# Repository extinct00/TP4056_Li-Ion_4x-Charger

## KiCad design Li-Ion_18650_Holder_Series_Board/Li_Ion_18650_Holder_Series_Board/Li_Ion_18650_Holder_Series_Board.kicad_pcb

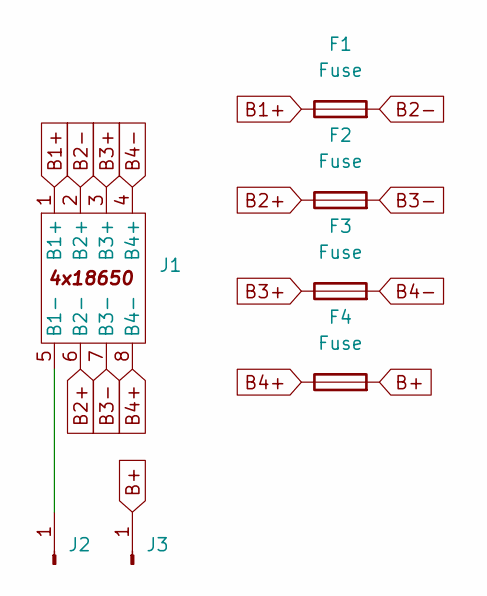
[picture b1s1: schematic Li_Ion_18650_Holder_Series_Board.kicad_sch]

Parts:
F1, F2, F3, F4: Fuse; Fuse_0603_1608Metric; LCSC C41380234
J1: 4xCellHolder_18650
J2, J3: Conn_01x01_Pin; Faston_C27636945; LCSC C27636945

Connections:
B1+: F1.1, J1.1 (B1+)
B2+: F2.1, J1.6 (B2-)
B2-: F1.2, J1.2 (B2+)
B3+: F3.1, J1.3 (B3+)
B3-: F2.2, J1.7 (B3-)
B4+: F4.1, J1.8 (B4-)
B4-: F3.2, J1.4 (B4+)
B+: F4.2, J3.1
unnamed: J1.5 (B1-), J2.1

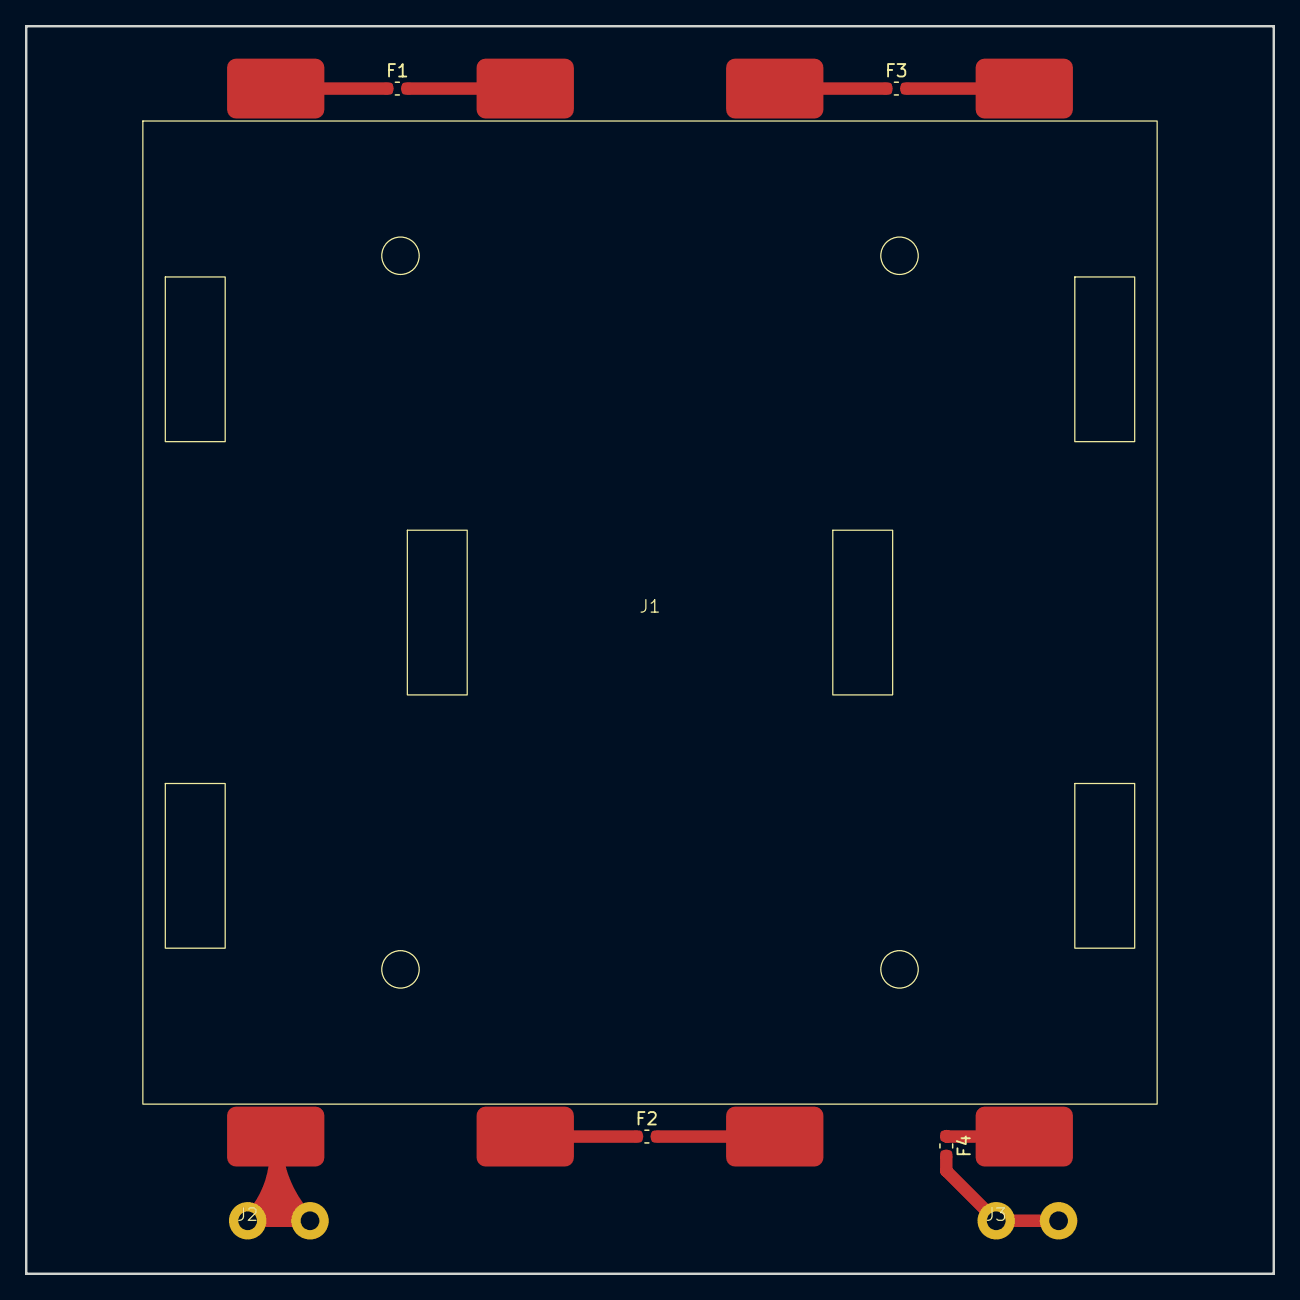
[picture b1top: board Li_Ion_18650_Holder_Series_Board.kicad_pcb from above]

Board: 2 copper layers, 100.0 x 100.0 mm, 7 parts (0 on the bottom side), 9 nets.

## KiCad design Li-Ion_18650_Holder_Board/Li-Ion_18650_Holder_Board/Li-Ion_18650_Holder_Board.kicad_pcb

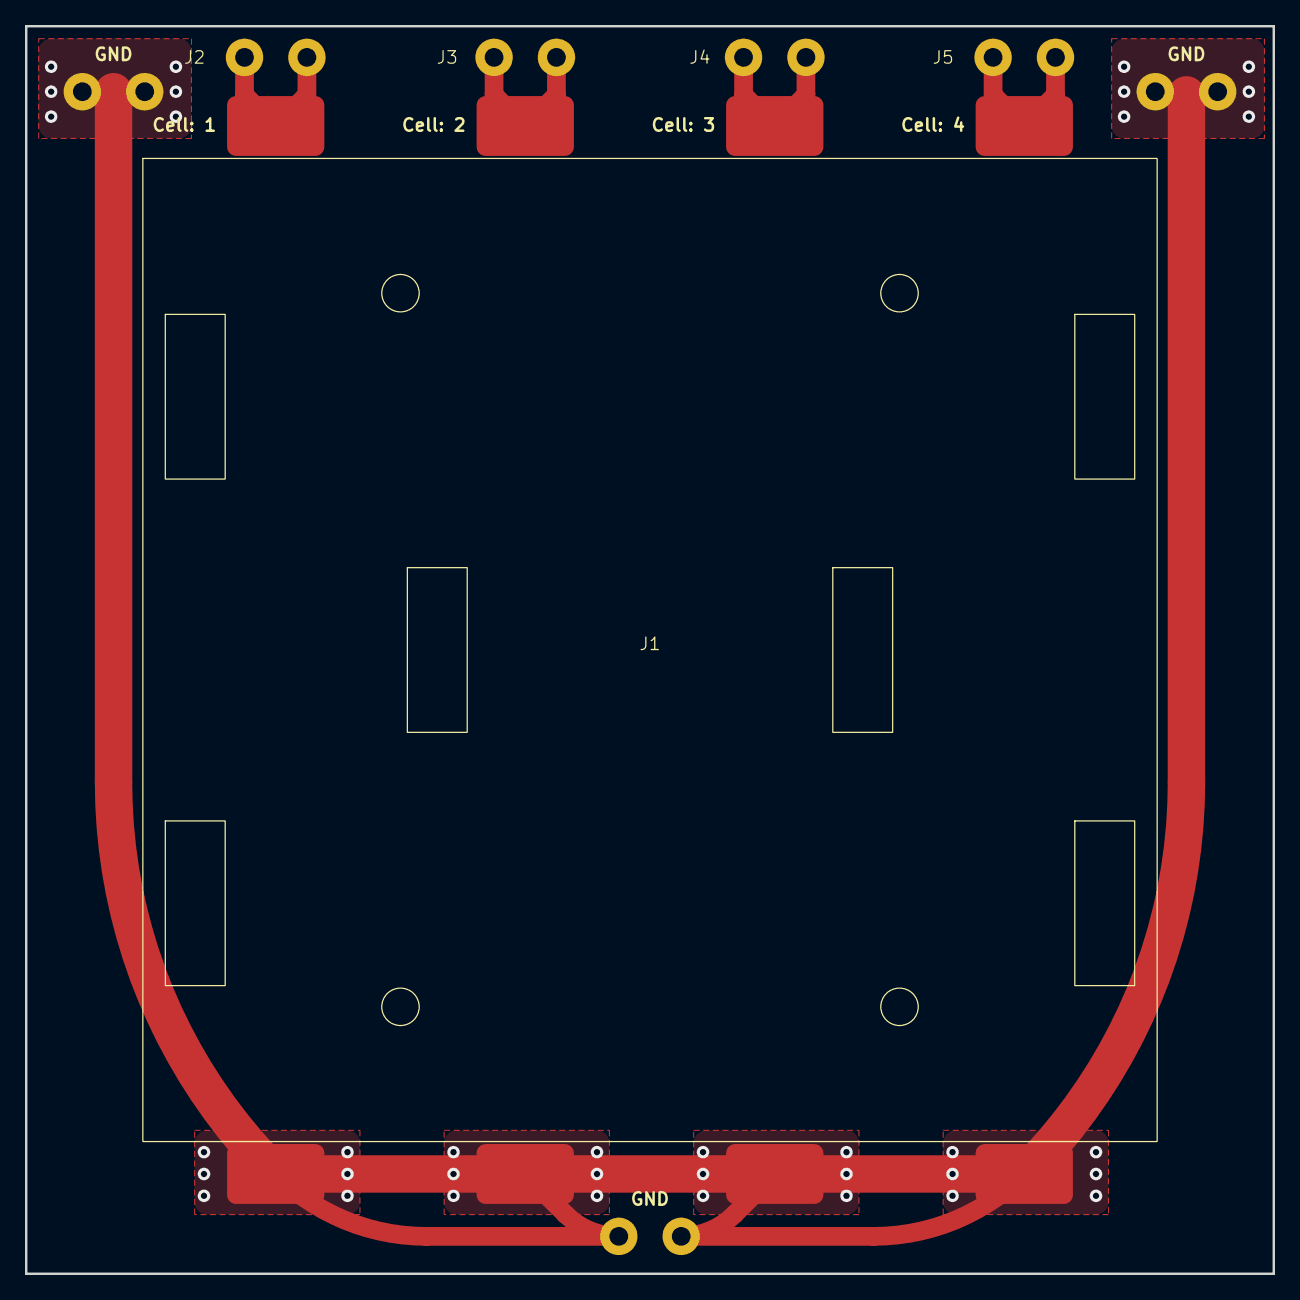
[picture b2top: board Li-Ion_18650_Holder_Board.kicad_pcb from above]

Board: 2 copper layers, 100.0 x 100.0 mm, 8 parts (0 on the bottom side), 5 nets.

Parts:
GND: Conn_01x01_Pin; Faston_C27636945
GND#2, GND#3: Conn_01x01_Pin; Faston_C27636945
J1: 4xCellHolder_18650
J2, J3, J4, J5: Conn_01x01_Pin; Faston_C27636945

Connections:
GND: GND.1, GND#2.1, GND#3.1, J1.5 (B1-), J1.6 (B2-), J1.7 (B3-), J1.8 (B4-)
unnamed: J1.1 (B1+), J2.1
unnamed: J1.2 (B2+), J3.1
unnamed: J1.3 (B3+), J4.1
unnamed: J1.4 (B4+), J5.1

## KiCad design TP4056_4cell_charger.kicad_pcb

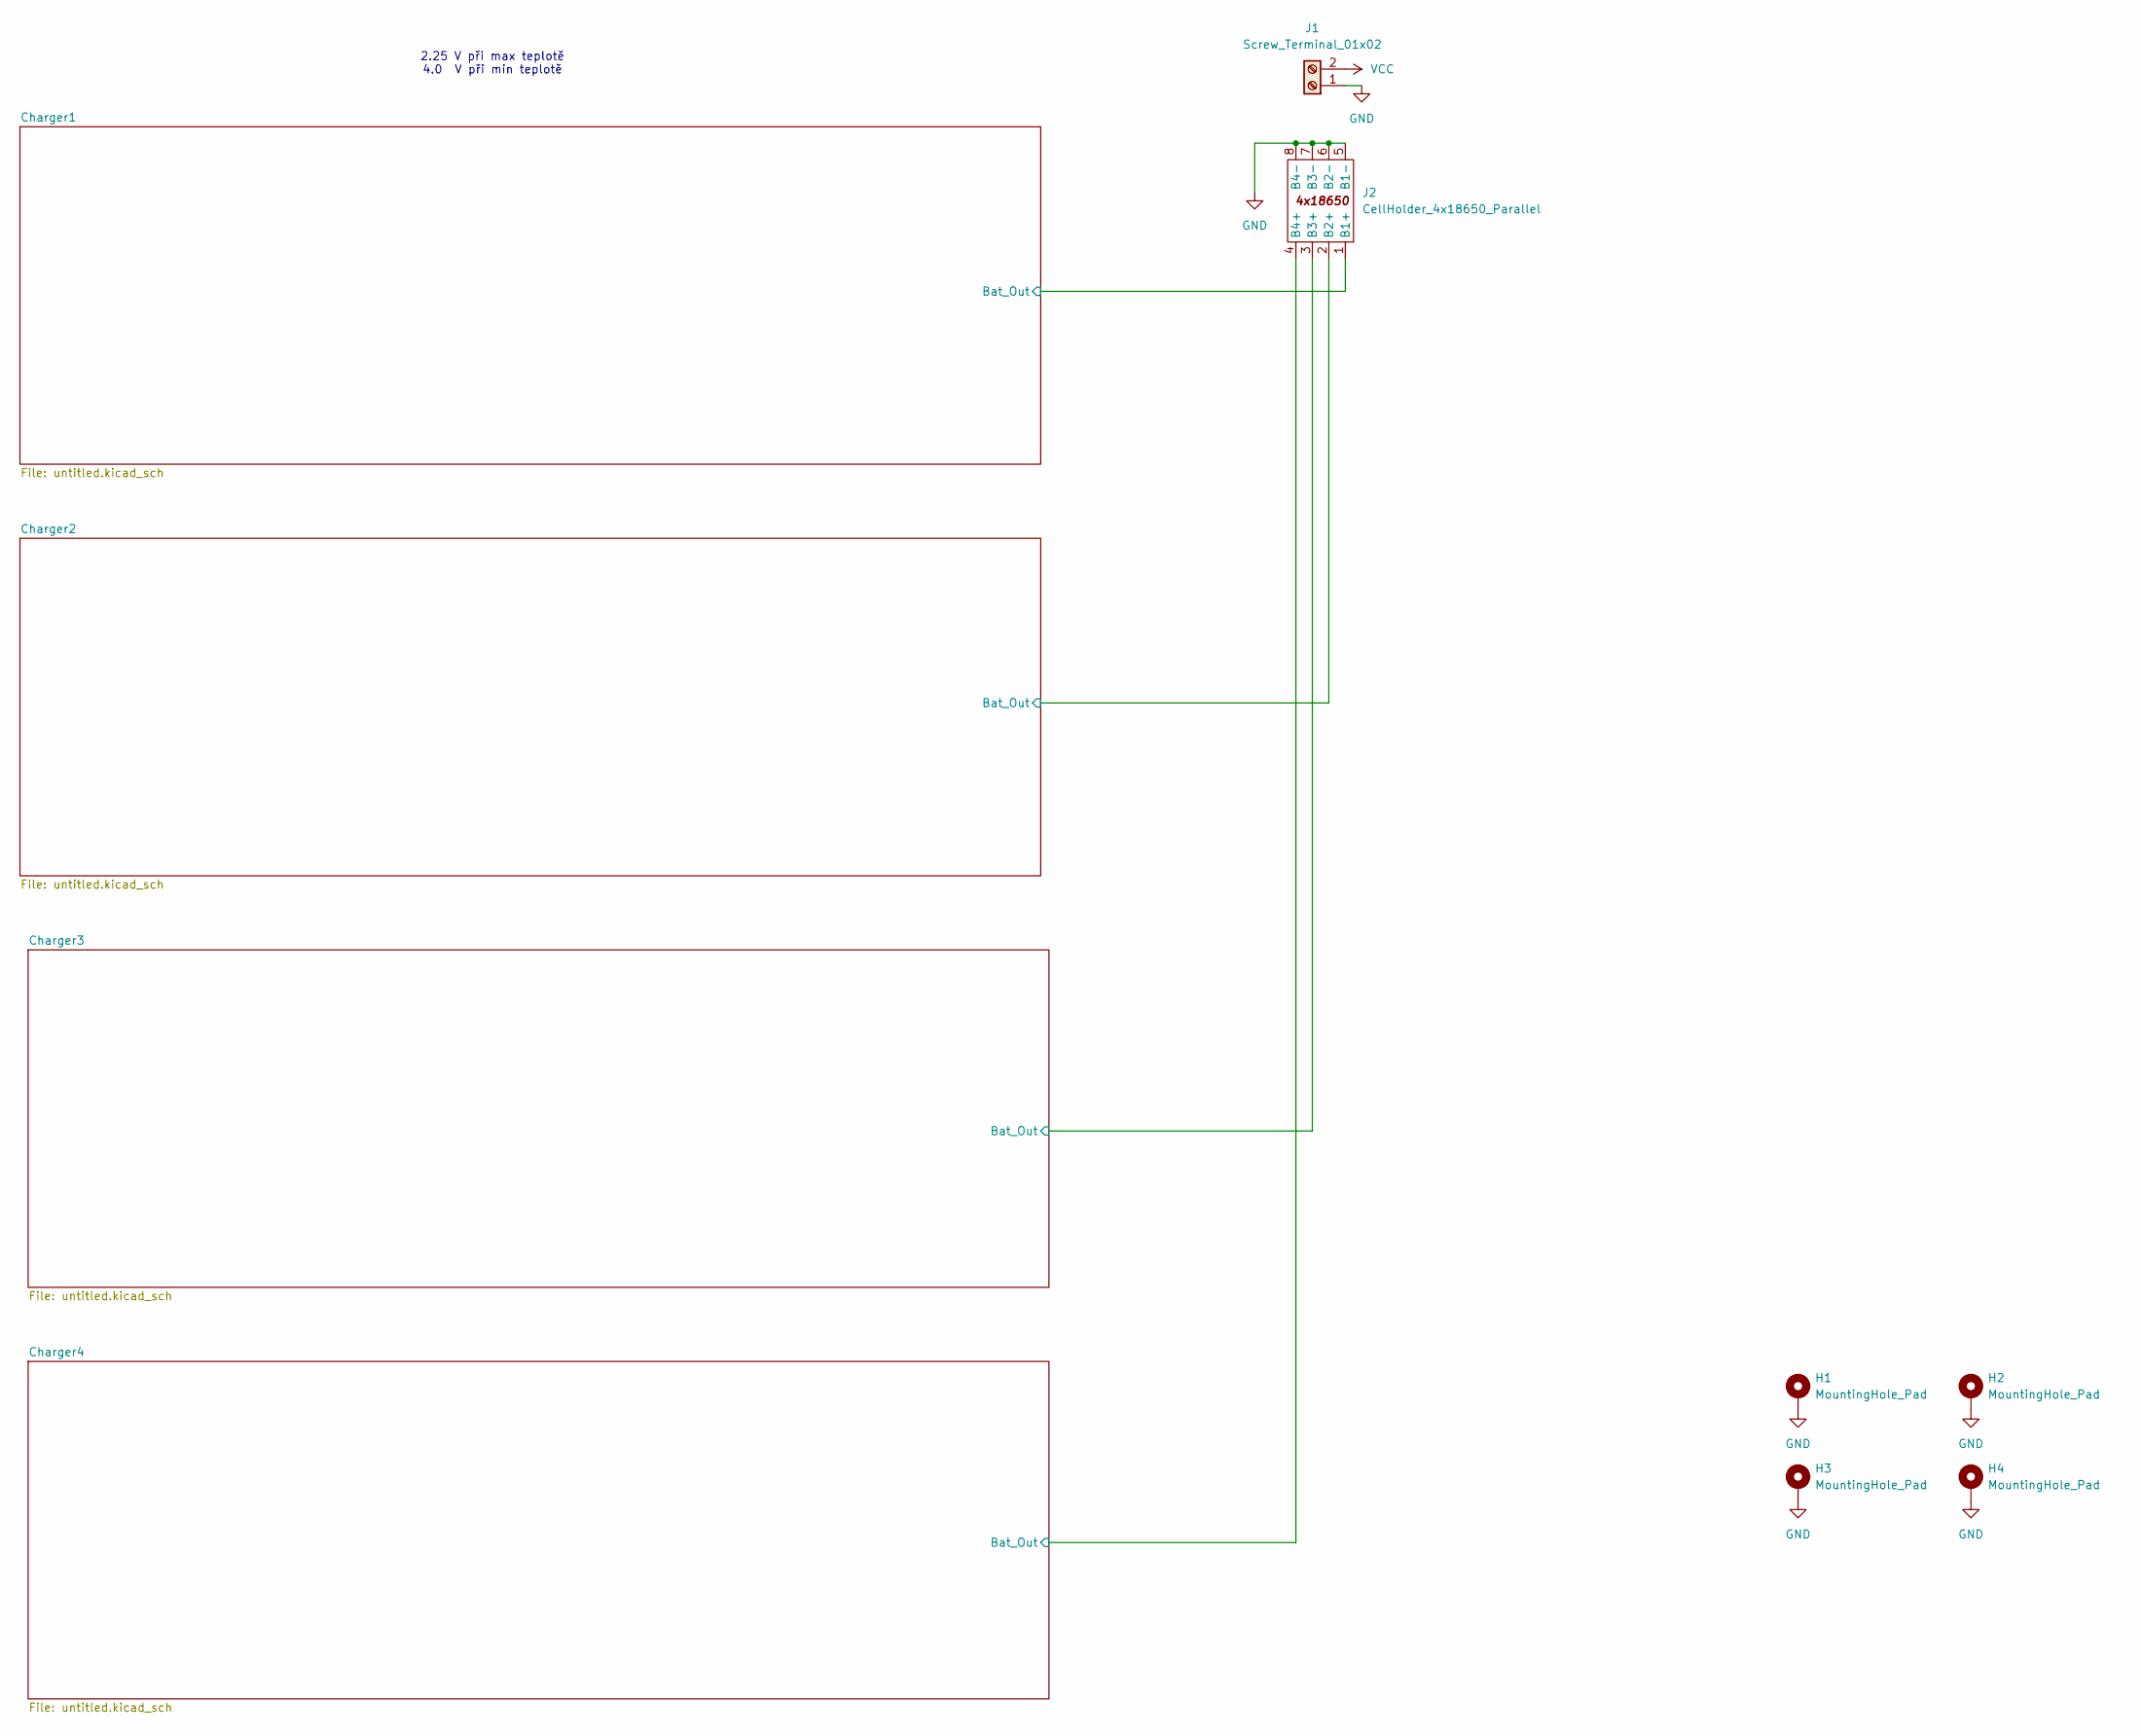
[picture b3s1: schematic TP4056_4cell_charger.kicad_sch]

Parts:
H1, H2, H3, H4: MountingHole_Pad; MountingHole_3.2mm_M3_Pad_Via
J1: Screw_Terminal_01x02; TerminalBlock_Phoenix_MKDS-1,5-2-5.08_1x02_P5.08mm_Horizont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; LCSC C8465
J2: CellHolder_4x18650_Parallel; 4xCellHolder_18650

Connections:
/Charger1/Bat_Out: J2.1 (B1+); also elsewhere on the board
/Charger2/Bat_Out: J2.2 (B2+); also elsewhere on the board
/Charger3/Bat_Out: J2.3 (B3+); also elsewhere on the board
/Charger4/Bat_Out: J2.4 (B4+); also elsewhere on the board
GND: H1.1, H2.1, H3.1, H4.1, J1.1, J2.5 (B1-), J2.6 (B2-), J2.7 (B3-), J2.8 (B4-); also elsewhere on the board
VCC: J1.2; also elsewhere on the board

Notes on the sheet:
2.25 V při max teplotě 4.0 V při min teplotě

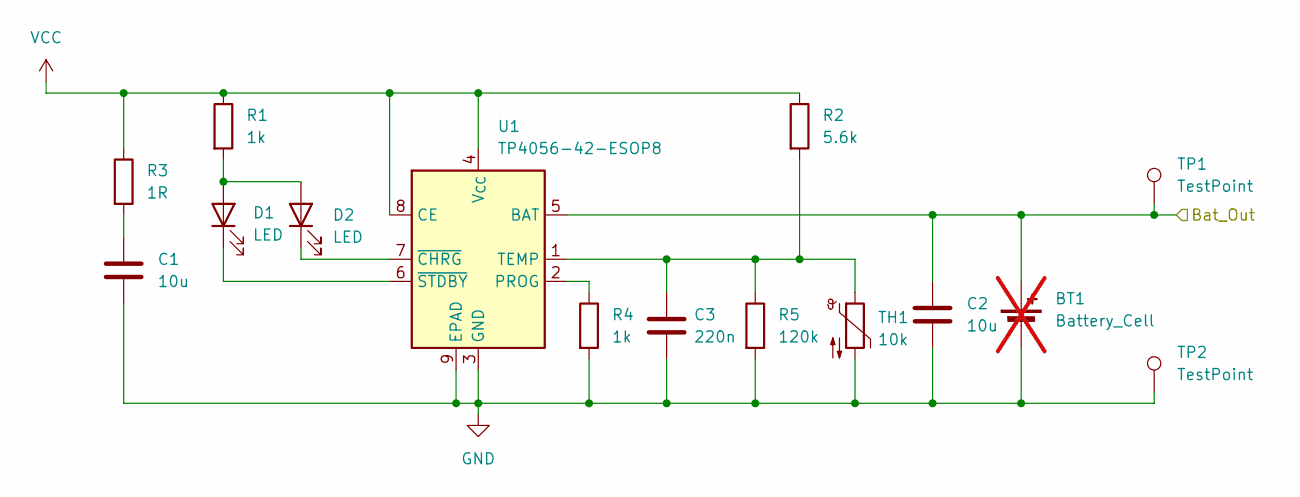
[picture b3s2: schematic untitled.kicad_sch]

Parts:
BT1: Battery_Cell; not fitted
C1, C2: 10u; C_0603_1608Metric; LCSC C19702
C3: 220n; C_0603_1608Metric; LCSC C64705
D1: LED; LED_0603_1608Metric; LCSC C965807
D2: LED; LED_0603_1608Metric; LCSC C965799
R1, R4: 1k; R_0603_1608Metric; LCSC C22548
R2: 5.6k; R_0603_1608Metric; LCSC C114627
R3: 1R; R_0603_1608Metric; LCSC C112305
R5: 120k; R_0603_1608Metric; LCSC C114607
TH1: 10k; R_0603_1608Metric; LCSC C13564
TP1, TP2: TestPoint; TestPoint_Pad_4.0x4.0mm
U1: TP4056-42-ESOP8; SOIC-8-1EP_3.9x4.9mm_P1.27mm_EP2.41x3.3mm_ThermalVias; LCSC C382139

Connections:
/Charger1/Bat_Out: C2.1, TP1.1, U1.5 (BAT); also elsewhere on the board
GND: BT1.2 (-), C1.2, C2.2, C3.2, R4.2, R5.2, TH1.2, TP2.1, U1.3 (GND), U1.9 (EPAD); also elsewhere on the board
unnamed: C1.1, R3.2
unnamed: D1.2 (A), D2.2 (A), R1.2
unnamed: D1.1 (K), U1.6 (~STDBY)
unnamed: D2.1 (K), U1.7 (~CHRG)
unnamed: R4.1, U1.2 (PROG)
unnamed: C3.1, R2.2, R5.1, TH1.1, U1.1 (TEMP)
VCC: R1.1, R2.1, R3.1, U1.4 (V_{CC}), U1.8 (CE); also elsewhere on the board

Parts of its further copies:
C4, C5, C7, C8, C10, C11: 10u; C_0603_1608Metric; LCSC C19702
C6, C9, C12: 220n; C_0603_1608Metric; LCSC C64705
D3, D5, D7: LED; LED_0603_1608Metric; LCSC C965807
D4, D6, D8: LED; LED_0603_1608Metric; LCSC C965799
R6, R9, R11, R14, R16, R19: 1k; R_0603_1608Metric; LCSC C22548
R7, R12, R17: 5.6k; R_0603_1608Metric; LCSC C114627
R8, R13, R18: 1R; R_0603_1608Metric; LCSC C112305
R10, R15, R20: 120k; R_0603_1608Metric; LCSC C114607
TH2, TH3, TH4: 10k; R_0603_1608Metric; LCSC C13564
TP3, TP4, TP5, TP6, TP7, TP8: TestPoint; TestPoint_Pad_4.0x4.0mm
U2, U3, U4: TP4056-42-ESOP8; SOIC-8-1EP_3.9x4.9mm_P1.27mm_EP2.41x3.3mm_ThermalVias; LCSC C382139

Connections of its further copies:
/Charger2/Bat_Out: C5.1, TP3.1, U2.5 (BAT); also elsewhere on the board
/Charger3/Bat_Out: C8.1, TP5.1, U3.5 (BAT); also elsewhere on the board
/Charger4/Bat_Out: C11.1, TP7.1, U4.5 (BAT); also elsewhere on the board
GND: C4.2, C5.2, C6.2, C7.2, C8.2, C9.2, C10.2, C11.2, C12.2, R9.2, R10.2, R14.2, R15.2, R19.2, R20.2, TH2.2, TH3.2, TH4.2, TP4.1, TP6.1, TP8.1, U2.3 (GND), U2.9 (EPAD), U3.3 (GND), U3.9 (EPAD), U4.3 (GND), U4.9 (EPAD); also elsewhere on the board
unnamed: C4.1, R8.2
unnamed: C7.1, R13.2
unnamed: C10.1, R18.2
unnamed: D3.2 (A), D4.2 (A), R6.2
unnamed: D3.1 (K), U2.6 (~STDBY)
unnamed: D4.1 (K), U2.7 (~CHRG)
unnamed: D5.2 (A), D6.2 (A), R11.2
unnamed: D5.1 (K), U3.6 (~STDBY)
unnamed: D6.1 (K), U3.7 (~CHRG)
unnamed: D7.2 (A), D8.2 (A), R16.2
unnamed: D7.1 (K), U4.6 (~STDBY)
unnamed: D8.1 (K), U4.7 (~CHRG)
unnamed: R9.1, U2.2 (PROG)
unnamed: C6.1, R7.2, R10.1, TH2.1, U2.1 (TEMP)
unnamed: R14.1, U3.2 (PROG)
unnamed: C9.1, R12.2, R15.1, TH3.1, U3.1 (TEMP)
unnamed: R19.1, U4.2 (PROG)
unnamed: C12.1, R17.2, R20.1, TH4.1, U4.1 (TEMP)
VCC: R6.1, R7.1, R8.1, R11.1, R12.1, R13.1, R16.1, R17.1, R18.1, U2.4 (V_{CC}), U2.8 (CE), U3.4 (V_{CC}), U3.8 (CE), U4.4 (V_{CC}), U4.8 (CE); also elsewhere on the board

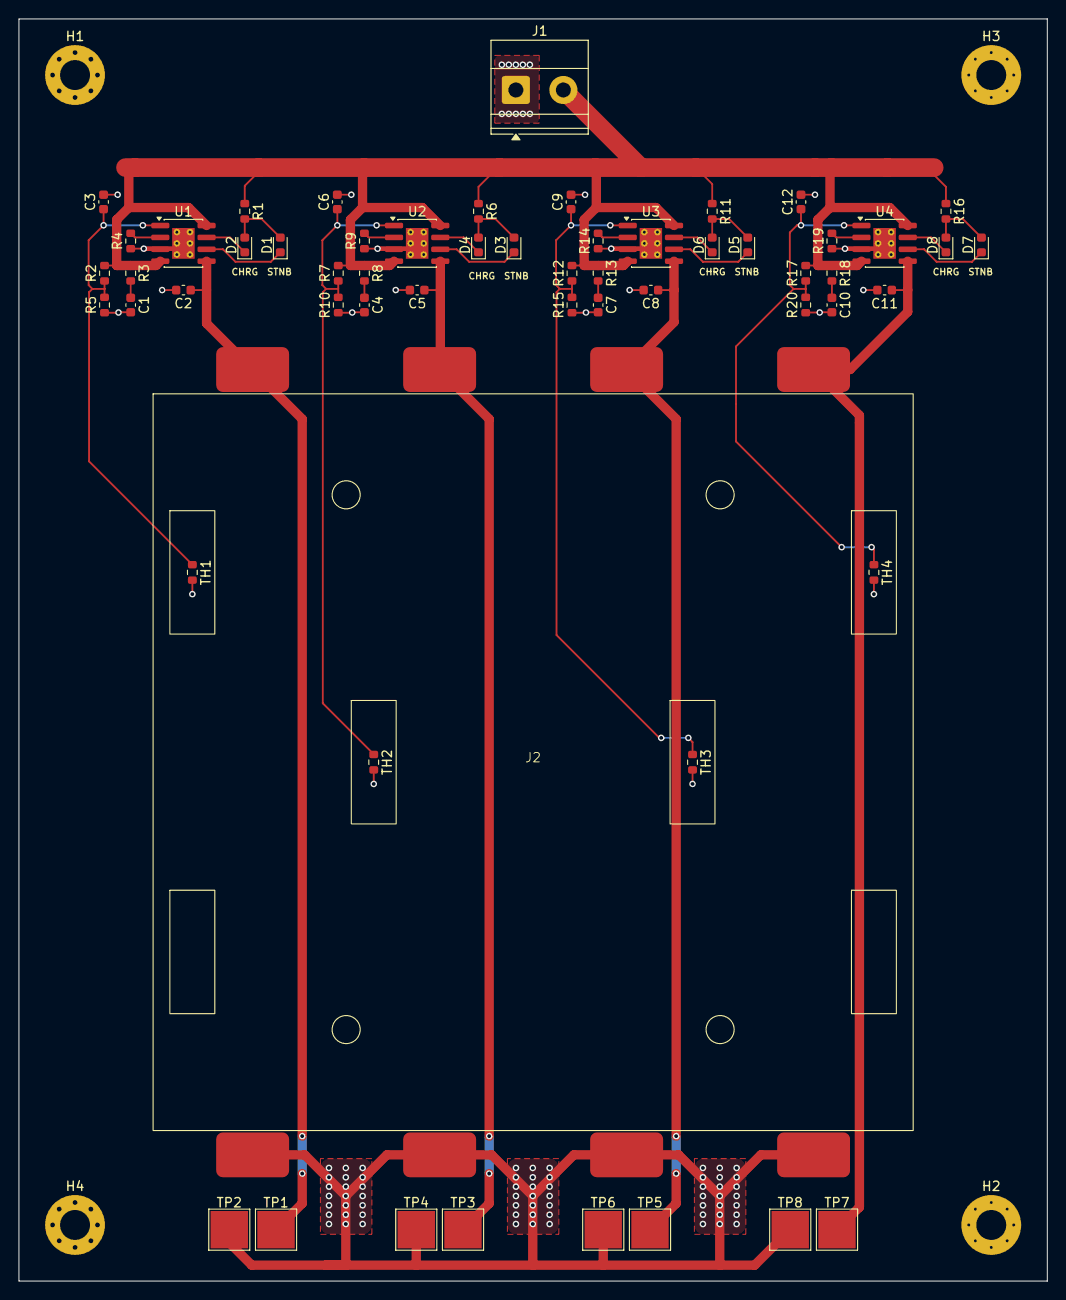
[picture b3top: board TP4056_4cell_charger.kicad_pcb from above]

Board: 2 copper layers, 110.0 x 135.0 mm, 62 parts (0 on the bottom side), 30 nets.

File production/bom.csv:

Designator,Footprint,Quantity,Value,LCSC Part #
"C1, C10, C11, C2, C4, C5, C7, C8",0603,8,10u,C19702
"C12, C3, C6, C9",0603,4,220n,
"D1, D3, D5, D7",0603,4,LED,C965807
"D2, D4, D6, D8",0603,4,LED,C965799
J1,"TerminalBlock_Phoenix_MKDS-1,5-2-5.08_1x02_P5.08mm_Horizontal",1,Screw_Terminal_01x02,C8465
J2,4xCellHolder_18650,1,CellHolder_4x18650_Parallel,
"R1, R11, R14, R16, R19, R4, R6, R9",0603,8,1k,C22548
"R10, R15, R20, R5",0603,4,120k,C114607
"R12, R17, R2, R7",0603,4,5.6k,C114627
"R13, R18, R3, R8",0603,4,1R,C112305
"TH1, TH2, TH3, TH4",0603,4,10k,C13564
"TP1, TP2, TP3, TP4, TP5, TP6, TP7, TP8",TestPoint_Pad_4.0x4.0mm,8,TestPoint,
"U1, U2, U3, U4",SOIC-8-1EP_3.9x4.9mm_P1.27mm_EP2.41x3.3mm_ThermalVias,4,TP4056-42-ESOP8,

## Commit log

2025-12-05 finished v1 layout
2025-12-06 finished v1 final version
2025-12-06 exported gerbers for v1
2025-12-07 finished v1, exported gerbers
2025-12-09 created sub_boards
2025-12-10 finished 18650 adapter layout
2025-12-10 finished layout
2025-12-10 working on layout
